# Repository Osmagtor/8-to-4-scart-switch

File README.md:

# 8-to-4 SCART Switch

<br>
<div align="center">
    <picture>
      
    </picture>
</div>
<br>

The "8-to-4 SCART Switch" is an open source PCB design for a passive SCART switch capable of (1) redirecting the signal of the selected SCART input device to the selected SCART output device and (2) selecting how the incoming signal is to be sent out (composite/RGB with composite sync or "csync"). It can accommodate for an RCA port to introduce a stereo audio signal or a lightgun signal into the selected output SCART cable.

This PCB was designed in response to the very limited number of output ports (normally 2) on the few SCART switches available for purchase that offer more than one. 

NOTE: this repository contains the KiCAD files for a PCB designed around the constraints detailed [here](#one-side-design). Thus, further adjustments may be necessary for different use-cases so feel free to modify the design so that it may better suit your needs or to expand its functionality. For this same reason, the .STL files for the case displayed in the picture above are not included.
## Table of Contents

* [PCB Breakdown](#pcb-breakdown)
	* [Multiple Inputs](#multiple-inputs)
	* [Multiple Outputs](#multiple-outputs)
	* [Multiple Inputs & Outputs](#multiple-inputs-&-outputs)
* [Known Issues & Limitations](#known-issues-&-limitations)
	* [One Side Design](#one-side-design)
	* [Single Input and Output](#single-input-and-output)
* [Links to the parts used](#links-to-the-parts-used)

## PCB Breakdown

### Multiple Inputs

The design of the board largely borrows from inexpensive dime in a dozen SCART switches that I have found in hardware stores, like the one pictured below, and whose overall quality I can vouch for after years of use.

The three spring-loaded push buttons labelled "A", "B" and "C" handle one of the SCART input ports each. These spring-loaded push buttons are made up of 18 pins grouped up in 2 columns of 3 pins each. The bottom pin in each column receives the signal from a different pin in the SCART port. Therefore, each group of 2 x 3 pins handles 2 pins, amounting to a total of 6 pins per spring-loaded push button: 

- SCART pin 2 (Right Audio In).
- SCART pin 6 (Left Audio In/ Mono Audio)
- SCART pin 7 (Blue).
- SCART pin 11 (Green).
- SCART pin 15 (Red).
- SCART pin 20 (Composite Video In).

When pushed down, the buttons connect the middle pins with the bottom pins. The incoming signal is then carried across all the other middle pins of the same type that lie between the button and the SCART output port by means of jump wires (hidden on the underside of the board behind some of the ports) and eventually makes it to the corresponding pin on the SCART output port.

It is worth noting that the "corresponding" pin is not always the same pin as in the SCART input port. The Red, Blue and Green video signals travel to the same pins. That is, they travel from pins 15, 11 and 7, respectively, to pins 15, 11 and 7. However, the Composite, Left Audio and Right Audio signals are "crosslinked". In other words, pin 20 (Composite Video In), pin 2 (Right Audio In) and pin 6 (Left Audio In/ Mono Audio) end up on pin 19 (Composite Video Out), pin 1 (Right Audio Out) and pin 3 (Left Audio Out/ Mono) at the other end of any SCART cable. This essentially means that pins 20, 2 and 6 on the SCART input ports have to be routed to pins 19, 1 and 3, respectively.

The two sets of RCA ports on the switch exploit this feature of the design of SCART cables. One of them is connected to all the output pins on the SCART output port, serving as a set of RCA input ports. This is very useful for consoles with mono audio, like the Sega MegaDrive/ Genesis, as the original mono audio signal can be replaced by the stereo audio from the console's headphone jack. Moreover, the Composite Video jack of this set can be used to introduce the signal of a lightgun in lieu of having to plug the lightgun into the TV. The other set of RCA ports is connected to all the input pins on the SCART output port, serving as a set of RCA output ports.

There is only two pins left to address: pin 8 (Status & Aspect Ratio) and pin 16 (RGB Selection). These are routed through separate common traces via 1N4148 diodes (on the underside of the board). Unlike all other pins, pins 8 and 16 carry higher voltages. Pin 8 sits between 5 and 8 V for a 16:9 aspect ratio and between 9.5 and 12 V for a 4:3 aspect ratio. Meanwhile, pin 16 sits between 0 and 0.4 V for a Composite Video Signal and between 1 and 3 V for a RGB Video signal with composite sync or "csync". 

While, the mechanism holding all spring-loaded push buttons together only allows one button to be pushed down at once, it is possible to brute force multiple switches into a pushed down state. As such, the diodes preclude any of the previous signals from feeding back into one another and causing any kind of mayhem. As to why these signals are not routed through the push buttons using sets of 24 pins instead, costs and/or availability may be to blame. When sourcing for these same type of push buttons for this project's PCB design, sets of 24 pin push buttons where much harder to come by and more expensive to boot. It could also be that the board only being printed one side, it couldn't accommodate for even more bespoke traces and all the ensuing jump wires.

Finally, the RGB push button on the switch simply allows the RGB signal through, telling the receiving device to use the signals from the RGB pins for video and the signal from the Composite Video pin as sync ("csync"). When the button is not pushed down, the RGB signal is cut off, telling the receiving device to use the signal from the Composite Video pin for the video signal. 
### Multiple Outputs

To be able to select between multiple outputs instead, it is necessary to change the directionality of the SCART switch described [above](#source-material). The necessary changes to achieve this were carried out on another identical switch by severing the necessary traces and bridging the necessary pins by means of wires. It is far from the most aesthetically-pleasing of solutions but it served as proof-of-concept.

For staters, the directionality of the crosslinked pins had to be reverted. Therefore, pin 20 (Composite Video In), pin 2 (Right Audio In) and pin 6 (Left Audio In/ Mono Audio) on the SCART input port were routed to pin 19 (Composite Video Out), pin 1 (Right Audio Out) and pin 3 (Left Audio Out/ Mono) on the SCART output ports. As the traces on the board were connected to the wrong pins, it was necessary to sever all the traces involved on either end and bypass them using spare wires. The RGB video pins, meanwhile, could be left intact since they connect to the same pins on both ends.

Pins 8 and 16 could not remain routed through their separate common traces. In their default configuration, the diodes would prevent any signal from coming through and simply changing their direction to allow for the signal to go through would defeat their purpose. After all, in doing so, all signals would go through at all times. Instead, the "RGB", "B-A" and "C-A" buttons were used to route these signals to the selected output, which involved further trace severing and wire soldering.

Therefore, to change the selected SCART output port, it was necessary to push down a button from each set. Pushing down the "C" button would send the RGB, Composite Video and Audio signals from the SCART input port to the third SCART output port, and pushing down the "C-A" button would send the Aspect Ratio and RGB-selection signal from the SCART input port to the third SCART output port too. In the photo below, you may more clearly observe how this worked. Note that the unmodified SCART switch is sitting behind and its output is daisy-chained to the SCART input port on the modified SCART switch.

The "RGB", "B-A" and "C-A" buttons were used since the "RGB" push-button was no longer needed for its intended purpose (after all, that was already handled by the same push-button on the 3-to-1 SCART switch) and the "B-A" and "C-A" push buttons were of no use to me.
### Multiple Inputs & Outputs

Designing a SCART switch with multiple input and output ports consisted of merging the design of (1) the inexpensive quality SCART switch that I had and (2) the other one whose directionality had successfully been reversed. 

The design of the area comprising the SCART input ports, the RCA ports and the RGB Selection push button was fairly straightforward. All that changed was the number of SCART ports, which was expanded from 3 to 8, and the output RCA port, which I completely removed as I had no real use for them.

As for the design of the area comprising the SCART output ports, a set of four 24 pin push buttons was used to bring into a single set of push buttons the signals that were controlled by the "RGB", "B-A" and "C-A" push buttons in the modified SCART switch.
## Known Issues & Limitations

First of all, the wiring that can be observed on the pictures [above](#merging-all-source-material) is the result of two minor design flaws that have since been corrected and a minor machining flaw:

* The traces that connect pins 8 and 16 were accidentally swapped around, requiring two traces to be severed and two wires to be soldered.
* The RCA connector was accidentally mirrored, causing a mismatch between the colours of the RCA ports and the pins they actually lead to.
* Owing to the levels of tolerance of the milling machine that made the board, two traces from the first SCART input port are permanently bridged, requiring the two traces to be severed and two wires to be soldered in their place.
### One Side Design 

Due to the sheer size of a PCB with this many ports, I only had access to machinery capable of making milled PCBs and the machinery in question could only mill on one side of the board, making it necessary to resort to jump wires like the SCART switches I used for reference.

This does not appear to affect any of the signals getting to the SCART output ports. At most, there is a nigh imperceptible loss of brightness that only my FrameMeister upscaler manages to pick up and which is only really noticeable on my Sega MegaDrive/ Genesis. Albeit it could be the result of the signal travelling over too many jump wires, this console uses a cheap RGB cable that might be to blame. The rest of my retro consoles are paired up with high quality RGB SCART cables from [Retro Gaming Cables](https://www.retrogamingcables.co.uk/).

Regardless, had it been possible to mill on the other side of the board, the pins connected by the jumper wires would have been connected to traces on the other side by means of vias. Needless to say, it would have made soldering easier and the end-result would have been nicer.

The pictures above are for you to form your own opinion. They are screenshots taken using a FrameMeister upscaler. The only difference between each screenshot lies on how far the SCART signal has had to travel: 

* "Frameister" means that the console's SCART cable has been directly plugged into the FrameMeister.
* "Switch v1" refers to the proof-of-concept switch that was modified to have its directionality reversed. In this case, the console's SCART cable was plugged into the unmodified switch, which, in turn, was daisy-chained into the modified switch whose output was then plugged into the FrameMeister.
* "Switch v2" refers to this project's switch.

In both cases, for "longest distance" screenshots the console's SCART cable and the SCART output cable have been set as far apart as possible, forcing the signal to travel the greatest length of jump wires possible. For "shortest distance" screenshots both cables have been set as close as possible to one another so that the signal has to travel the least. 

To my untrained eye, this does not appear to make much of a difference, not even in "Switch v1" screenshots, where the signal had to travel through an extra SCART cable connecting two switches.
### Single Input and Output

As a passive SCART switch by design, it is not possible to redirect the selected SCART input device to more than one SCART  output device. While more than one push button can be brute forced into a pushed down state, it would be necessary to boost the incoming image somehow for it to show correctly or even show at all in all devices. This would require a source of external power.

Lastly, due to the simplicity of the design of the board, it is not possible to mix and match inputs and outputs. A single selected input can only be routed to a single selected output.
## Links to the parts used

* [1x RCA port](https://es.aliexpress.com/item/1005006295411086.html?algo_exp_id=1704070b-437d-4806-bd52-9b4e4fd31481-30&pdp_npi=4%40dis%21EUR%215.68%211.82%21%21%2143.37%2113.88%21%40211b612517121802582044392eeff7%2112000036647428960%21sea%21ES%214782931422%21&curPageLogUid=3xNMGX6dJbsL&utparam-url=scene%3Asearch%7Cquery_from%3A)
* [12x female SCART ports](https://es.aliexpress.com/item/1005006636475708.html?algo_exp_id=9e1a5876-f124-43f7-b40c-11d20e1f46cf-22&pdp_npi=4%40dis%21EUR%211.55%211.45%21%21%211.63%211.52%21%40211b617a17121800592552603eb1fc%2112000037887909284%21sea%21ES%214782931422%21&curPageLogUid=zIvDoxFjqDd9&utparam-url=scene%3Asearch%7Cquery_from%3A)
* [1x 8 pin spring-loaded push button](https://es.aliexpress.com/item/1005006186944454.html?pvid=55b27e62-d06f-4987-be3b-784640dc741e&_t=gps-id%3ApcDetailTopMoreOtherSeller%2Cscm-url%3A1007.40000.327270.0%2Cpvid%3A55b27e62-d06f-4987-be3b-784640dc741e%2Ctpp_buckets%3A668%232846%238111%231996&pdp_npi=4%40dis%21EUR%213.44%211.03%21%21%2126.29%217.89%21%402103871e17121795811912119eab58%2112000036185800227%21rec%21ES%214782931422%21&utparam-url=scene%3ApcDetailTopMoreOtherSeller%7Cquery_from%3A)
* [1 set of 8 18 pin spring-loaded push buttons](https://es.aliexpress.com/item/32977337144.html?pvid=ed7a91a2-8967-4df6-9983-d61c363a6160&_t=gps-id%3ApcDetailTopMoreOtherSeller%2Cscm-url%3A1007.40000.327270.0%2Cpvid%3Aed7a91a2-8967-4df6-9983-d61c363a6160%2Ctpp_buckets%3A668%232846%238110%231995&pdp_npi=4%40dis%21EUR%212.83%212.83%21%21%212.98%212.98%21%402103871e17121797616365716eab58%2112000030624642228%21rec%21ES%214782931422%21&utparam-url=scene%3ApcDetailTopMoreOtherSeller%7Cquery_from%3A)
* [1 set of 4 24 pin spring-loaded push buttons](https://es.aliexpress.com/item/1005005575498175.html?gatewayAdapt=glo2esp)

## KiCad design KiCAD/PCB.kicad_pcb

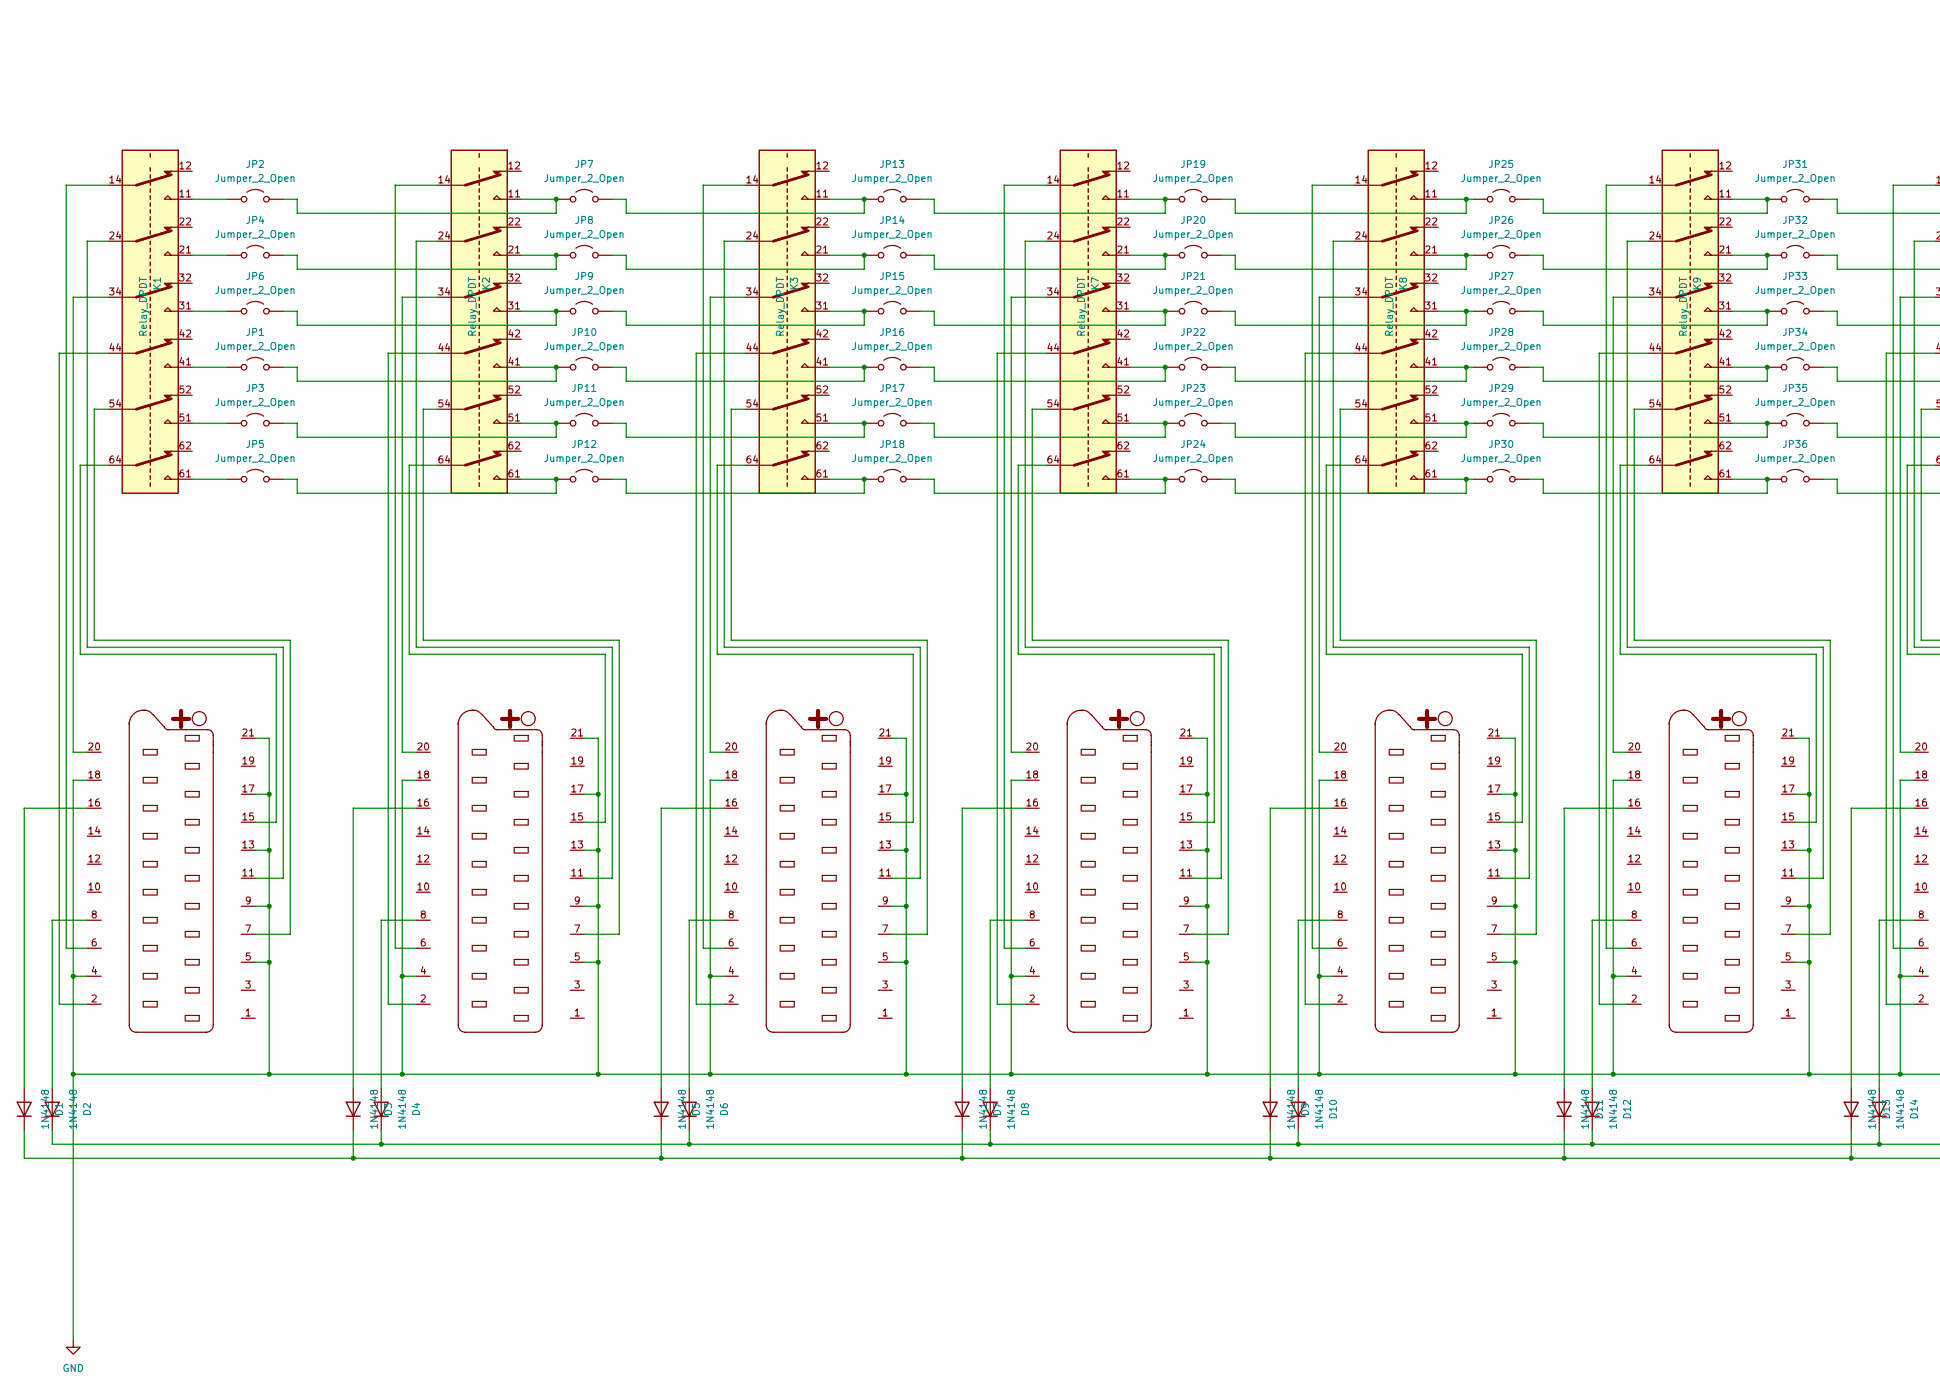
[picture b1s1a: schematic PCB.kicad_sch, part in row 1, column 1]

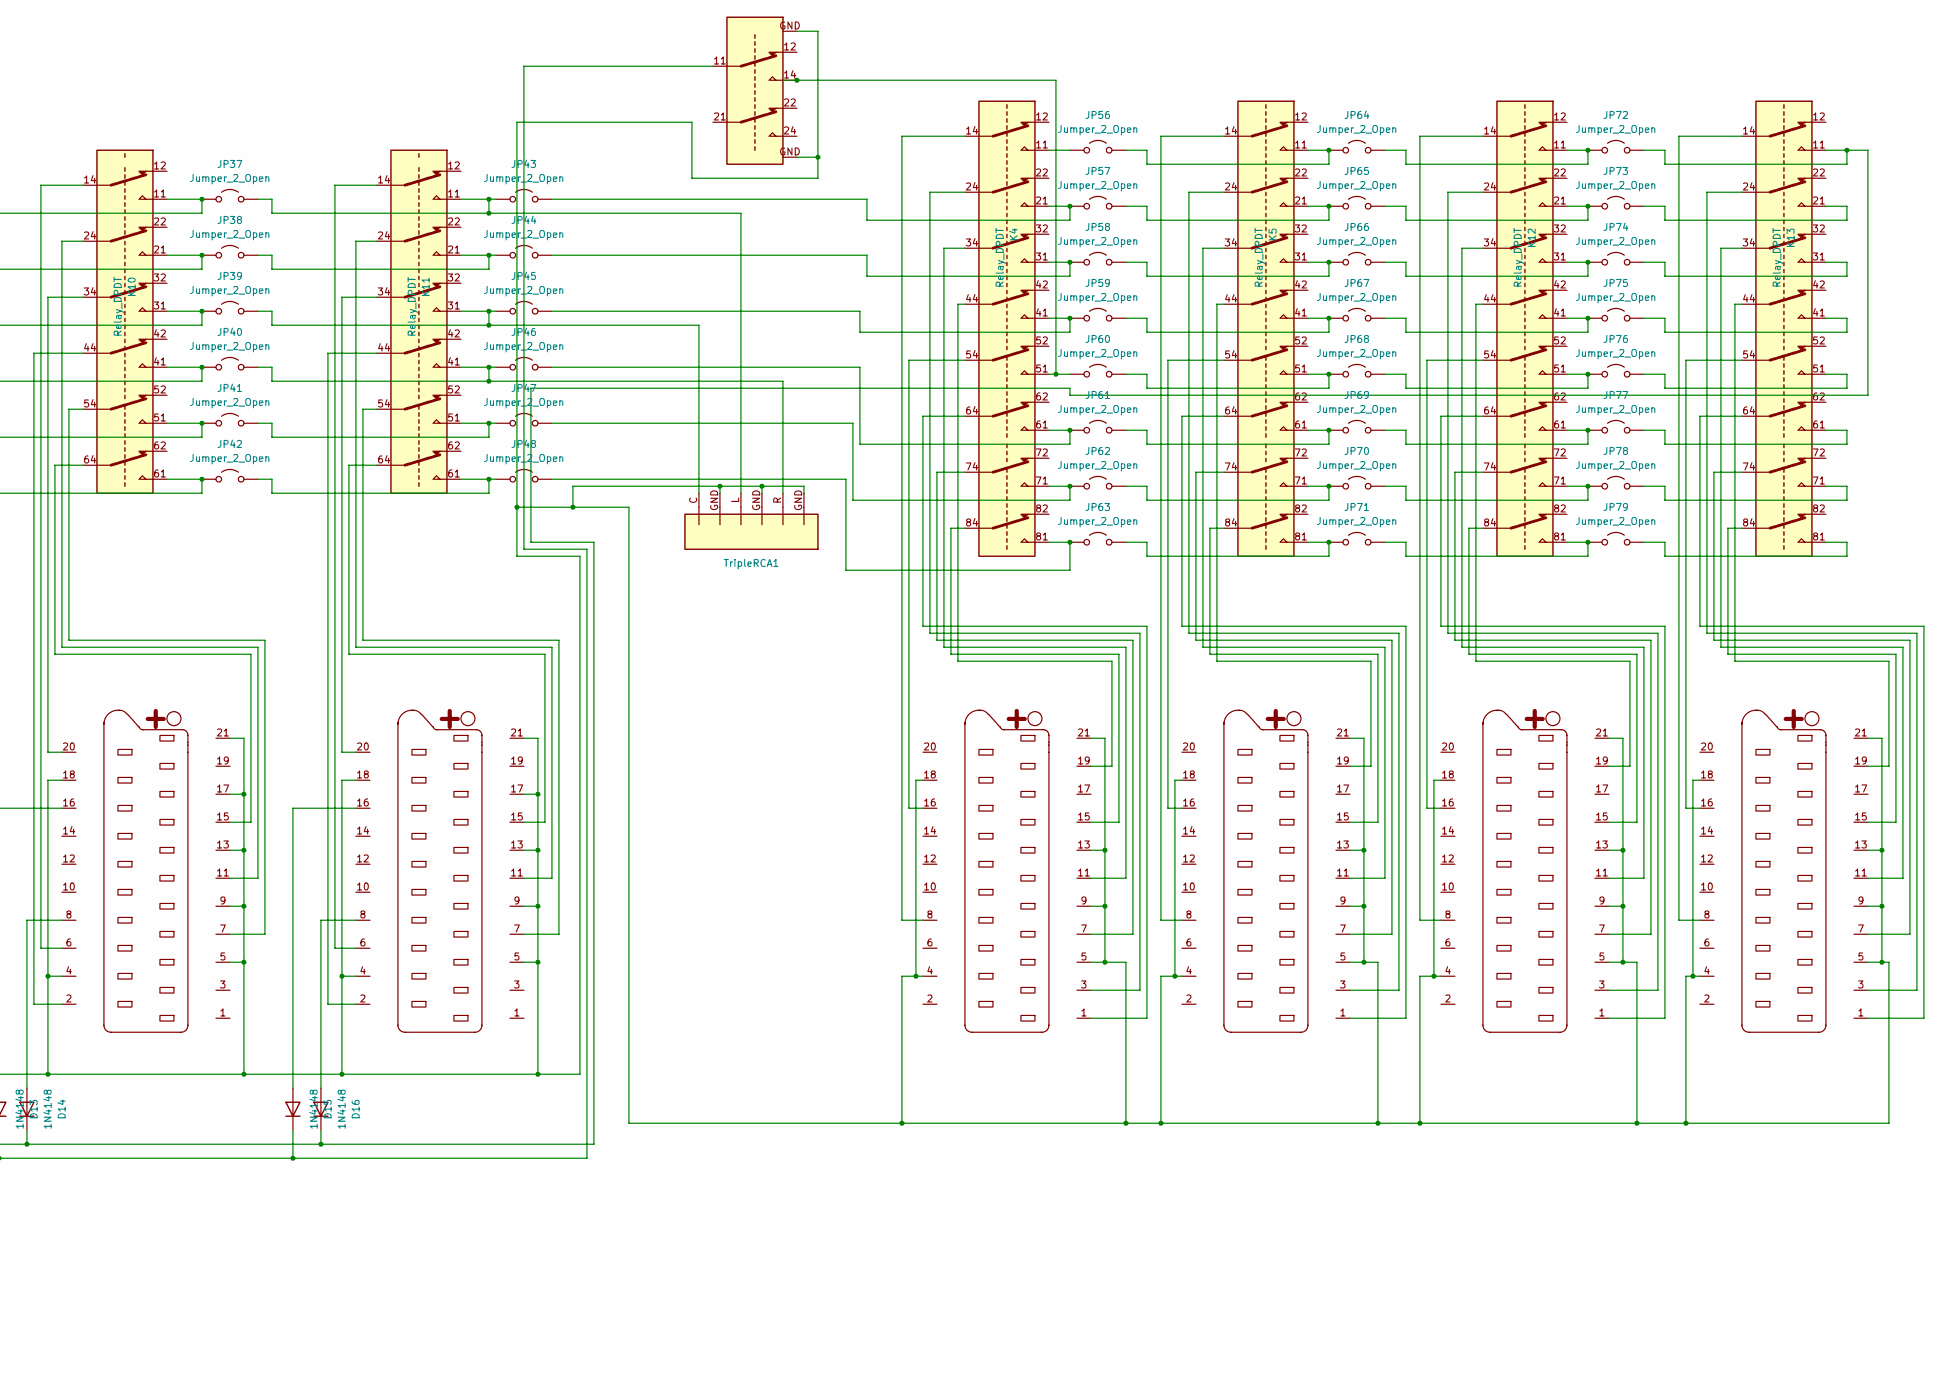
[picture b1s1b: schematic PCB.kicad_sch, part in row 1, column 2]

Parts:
D1, D2, D3, D4, D5, D6, D7, D8, D9, D10, D11, D12, D13, D14, D15, D16: 1N4148; D_DO-35_SOD27_P7.62mm_Horizontal
J1, J2, J3, J4, J5, J6, J7, J8, J9, J10, J11, J12: SCART-F; SCART
JP1, JP2, JP3, JP4, JP5, JP6, JP7, JP8, JP9, JP10, JP11, JP12, JP13, JP14, JP15, JP16, JP17, JP18, JP19, JP20, JP21, JP22, JP23, JP24, JP25, JP26, JP27, JP28, JP29, JP30, JP31, JP32, JP33, JP34, JP35, JP36, JP37, JP38, JP39, JP40, JP41, JP42, JP56, JP57, JP58, JP59, JP60, JP61, JP62, JP63, JP64, JP65, JP66, JP67, JP68, JP69, JP70, JP71, JP72, JP73, JP74, JP75, JP76, JP77, JP78, JP79: Jumper_2_Open; Jumper-Wire_12mm_Red
JP43, JP44, JP45, JP46, JP47, JP48: Jumper_2_Open; Jumper-Wire_20mm_Blue
K1, K2, K3, K7, K8, K9, K10, K11: Relay_DPDT; 18-PIN RELAY
K4, K5, K12, K13: Relay_DPDT; 24-PIN RELAY
K6: Relay_DPDT; Relay_DPDT_RGB_ONOFF
TripleRCA1: Triple_RCA

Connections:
GND: J1.4, J1.5, J1.9, J1.13, J1.17, J1.18, J1.21, J2.4, J2.5, J2.9, J2.13, J2.17, J2.18, J2.21, J3.4, J3.5, J3.9, J3.13, J3.17, J3.18, J3.21, J4.4, J4.5, J4.9, J4.13, J4.18, J4.21, J5.4, J5.5, J5.9, J5.13, J5.18, J5.21, J6.4, J6.5, J6.9, J6.13, J6.17, J6.18, J6.21, J7.4, J7.5, J7.9, J7.13, J7.17, J7.18, J7.21, J8.4, J8.5, J8.9, J8.13, J8.17, J8.18, J8.21, J9.4, J9.5, J9.9, J9.13, J9.17, J9.18, J9.21, J10.4, J10.5, J10.9, J10.13, J10.17, J10.18, J10.21, J11.4, J11.5, J11.9, J11.13, J11.18, J11.21, J12.4, J12.5, J12.9, J12.13, J12.18, J12.21, K6.GND, TripleRCA1.GND
unnamed: D1.2 (A), J1.16
unnamed: D1.1 (K), D3.1 (K), D5.1 (K), D7.1 (K), D9.1 (K), D11.1 (K), D13.1 (K), D15.1 (K), K6.11
unnamed: D2.2 (A), J1.8
unnamed: D3.2 (A), J2.16
unnamed: D4.2 (A), J2.8
unnamed: D5.2 (A), J3.16
unnamed: D6.2 (A), J3.8
unnamed: D7.2 (A), J6.16
unnamed: D8.2 (A), J6.8
unnamed: D9.2 (A), J7.16
unnamed: D10.2 (A), J7.8
unnamed: D2.1 (K), D4.1 (K), D6.1 (K), D8.1 (K), D10.1 (K), D12.1 (K), D14.1 (K), D16.1 (K), JP72.2 (B), K13.11
unnamed: D11.2 (A), J8.16
unnamed: D12.2 (A), J8.8
unnamed: D13.2 (A), J9.16
unnamed: D14.2 (A), J9.8
unnamed: D15.2 (A), J10.16
unnamed: D16.2 (A), J10.8
unnamed: J1.2, K1.44
unnamed: J1.6, K1.14
unnamed: J1.7, K1.54
unnamed: J1.11, K1.24
unnamed: J1.15, K1.64
unnamed: J1.20, K1.34
unnamed: J2.2, K2.44
unnamed: J2.6, K2.14
unnamed: J2.7, K2.54
unnamed: J2.11, K2.24
unnamed: J2.15, K2.64
unnamed: J2.20, K2.34
unnamed: J3.2, K3.44
unnamed: J3.6, K3.14
unnamed: J3.7, K3.54
unnamed: J3.11, K3.24
unnamed: J3.15, K3.64
unnamed: J3.20, K3.34
unnamed: J4.1, K4.64
unnamed: J4.3, K4.24
unnamed: J4.7, K4.74
unnamed: J4.8, K4.14
unnamed: J4.11, K4.34
unnamed: J4.15, K4.84
unnamed: J4.16, K4.54
unnamed: J4.19, K4.44
unnamed: J5.1, K5.64
unnamed: J5.3, K5.24
unnamed: J5.7, K5.74
unnamed: J5.8, K5.14
unnamed: J5.11, K5.34
unnamed: J5.15, K5.84
unnamed: J5.16, K5.54
unnamed: J5.19, K5.44
unnamed: J6.2, K7.44
unnamed: J6.6, K7.14
unnamed: J6.7, K7.54
unnamed: J6.11, K7.24
unnamed: J6.15, K7.64
unnamed: J6.20, K7.34
unnamed: J7.2, K8.44
unnamed: J7.6, K8.14
unnamed: J7.7, K8.54
unnamed: J7.11, K8.24
unnamed: J7.15, K8.64
unnamed: J7.20, K8.34
unnamed: J8.2, K9.44
unnamed: J8.6, K9.14
unnamed: J8.7, K9.54
unnamed: J8.11, K9.24
unnamed: J8.15, K9.64
unnamed: J8.20, K9.34
unnamed: J9.2, K10.44
unnamed: J9.6, K10.14
unnamed: J9.7, K10.54
unnamed: J9.11, K10.24
unnamed: J9.15, K10.64
unnamed: J9.20, K10.34
unnamed: J10.2, K11.44
unnamed: J10.6, K11.14
unnamed: J10.7, K11.54
unnamed: J10.11, K11.24
unnamed: J10.15, K11.64
unnamed: J10.20, K11.34
unnamed: J11.1, K12.64
unnamed: J11.3, K12.24
unnamed: J11.7, K12.74
unnamed: J11.8, K12.14
unnamed: J11.11, K12.34
unnamed: J11.15, K12.84
unnamed: J11.16, K12.54
unnamed: J11.19, K12.44
unnamed: J12.1, K13.64
unnamed: J12.3, K13.24
unnamed: J12.7, K13.74
unnamed: J12.8, K13.14
unnamed: J12.11, K13.34
unnamed: J12.15, K13.84
unnamed: J12.16, K13.54
unnamed: J12.19, K13.44
unnamed: JP1.1 (A), K1.41
unnamed: JP1.2 (B), JP10.1 (A), K2.41
unnamed: JP2.1 (A), K1.11
unnamed: JP2.2 (B), JP7.1 (A), K2.11
unnamed: JP3.1 (A), K1.51
unnamed: JP4.1 (A), K1.21
unnamed: JP4.2 (B), JP8.1 (A), K2.21
unnamed: JP5.1 (A), K1.61
unnamed: JP6.1 (A), K1.31
unnamed: JP6.2 (B), JP9.1 (A), K2.31
unnamed: JP10.2 (B), JP16.1 (A), K3.41
unnamed: JP3.2 (B), JP11.1 (A), K2.51
unnamed: JP11.2 (B), JP17.1 (A), K3.51
unnamed: JP5.2 (B), JP12.1 (A), K2.61
unnamed: JP12.2 (B), JP18.1 (A), K3.61
unnamed: JP7.2 (B), JP13.1 (A), K3.11
unnamed: JP13.2 (B), JP19.1 (A), K7.11
unnamed: JP8.2 (B), JP14.1 (A), K3.21
unnamed: JP14.2 (B), JP20.1 (A), K7.21
unnamed: JP9.2 (B), JP15.1 (A), K3.31
unnamed: JP15.2 (B), JP21.1 (A), K7.31
unnamed: JP16.2 (B), JP22.1 (A), K7.41
unnamed: JP17.2 (B), JP23.1 (A), K7.51
unnamed: JP18.2 (B), JP24.1 (A), K7.61
unnamed: JP19.2 (B), JP25.1 (A), K8.11
unnamed: JP20.2 (B), JP26.1 (A), K8.21
unnamed: JP21.2 (B), JP27.1 (A), K8.31
unnamed: JP22.2 (B), JP28.1 (A), K8.41
unnamed: JP23.2 (B), JP29.1 (A), K8.51
unnamed: JP24.2 (B), JP30.1 (A), K8.61
unnamed: JP25.2 (B), JP31.1 (A), K9.11
unnamed: JP26.2 (B), JP32.1 (A), K9.21
unnamed: JP27.2 (B), JP33.1 (A), K9.31
unnamed: JP28.2 (B), JP34.1 (A), K9.41
unnamed: JP29.2 (B), JP35.1 (A), K9.51
unnamed: JP30.2 (B), JP36.1 (A), K9.61
unnamed: JP31.2 (B), JP37.1 (A), K10.11
unnamed: JP32.2 (B), JP38.1 (A), K10.21
unnamed: JP33.2 (B), JP39.1 (A), K10.31
unnamed: JP34.2 (B), JP40.1 (A), K10.41
unnamed: JP35.2 (B), JP41.1 (A), K10.51
unnamed: JP36.2 (B), JP42.1 (A), K10.61
unnamed: JP37.2 (B), JP43.1 (A), K11.11, TripleRCA1.L
unnamed: JP38.2 (B), JP44.1 (A), K11.21
unnamed: JP39.2 (B), JP45.1 (A), K11.31, TripleRCA1.C
unnamed: JP40.2 (B), JP46.1 (A), K11.41, TripleRCA1.R
unnamed: JP41.2 (B), JP47.1 (A), K11.51
unnamed: JP42.2 (B), JP48.1 (A), K11.61
unnamed: JP43.2 (B), JP57.1 (A), K4.21
unnamed: JP44.2 (B), JP58.1 (A), K4.31
unnamed: JP45.2 (B), JP59.1 (A), K4.41
unnamed: JP46.2 (B), JP61.1 (A), K4.61
unnamed: JP47.2 (B), JP62.1 (A), K4.71
unnamed: JP48.2 (B), JP63.1 (A), K4.81
unnamed: JP56.1 (A), K4.11
unnamed: JP56.2 (B), JP64.1 (A), K5.11
unnamed: JP57.2 (B), JP65.1 (A), K5.21
unnamed: JP58.2 (B), JP66.1 (A), K5.31
unnamed: JP59.2 (B), JP67.1 (A), K5.41
unnamed: JP60.1 (A), K4.51, K6.14
unnamed: JP60.2 (B), JP68.1 (A), K5.51
unnamed: JP61.2 (B), JP69.1 (A), K5.61
unnamed: JP62.2 (B), JP70.1 (A), K5.71
unnamed: JP63.2 (B), JP71.1 (A), K5.81
unnamed: JP64.2 (B), JP72.1 (A), K12.11
unnamed: JP65.2 (B), JP73.1 (A), K12.21
unnamed: JP66.2 (B), JP74.1 (A), K12.31
unnamed: JP67.2 (B), JP75.1 (A), K12.41
unnamed: JP68.2 (B), JP76.1 (A), K12.51
unnamed: JP69.2 (B), JP77.1 (A), K12.61
unnamed: JP70.2 (B), JP78.1 (A), K12.71
unnamed: JP71.2 (B), JP79.1 (A), K12.81
unnamed: JP73.2 (B), K13.21
unnamed: JP74.2 (B), K13.31
unnamed: JP75.2 (B), K13.41
unnamed: JP76.2 (B), K13.51
unnamed: JP77.2 (B), K13.61
unnamed: JP78.2 (B), K13.71
unnamed: JP79.2 (B), K13.81

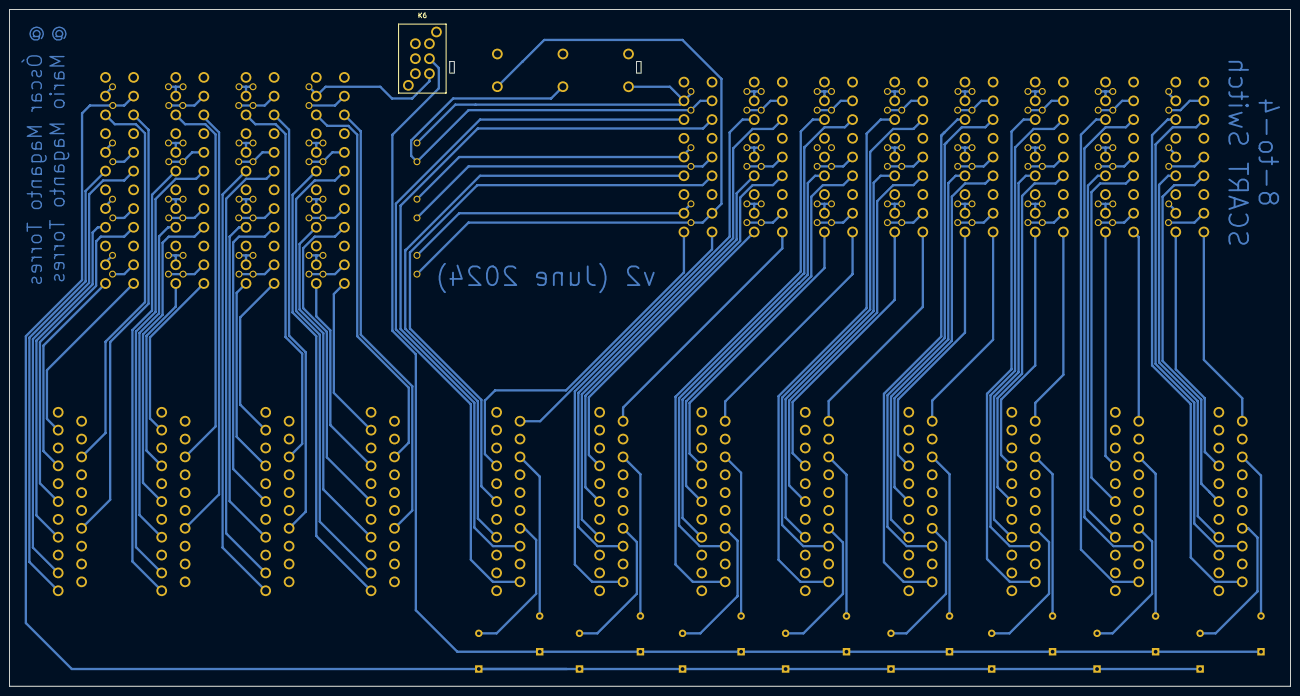
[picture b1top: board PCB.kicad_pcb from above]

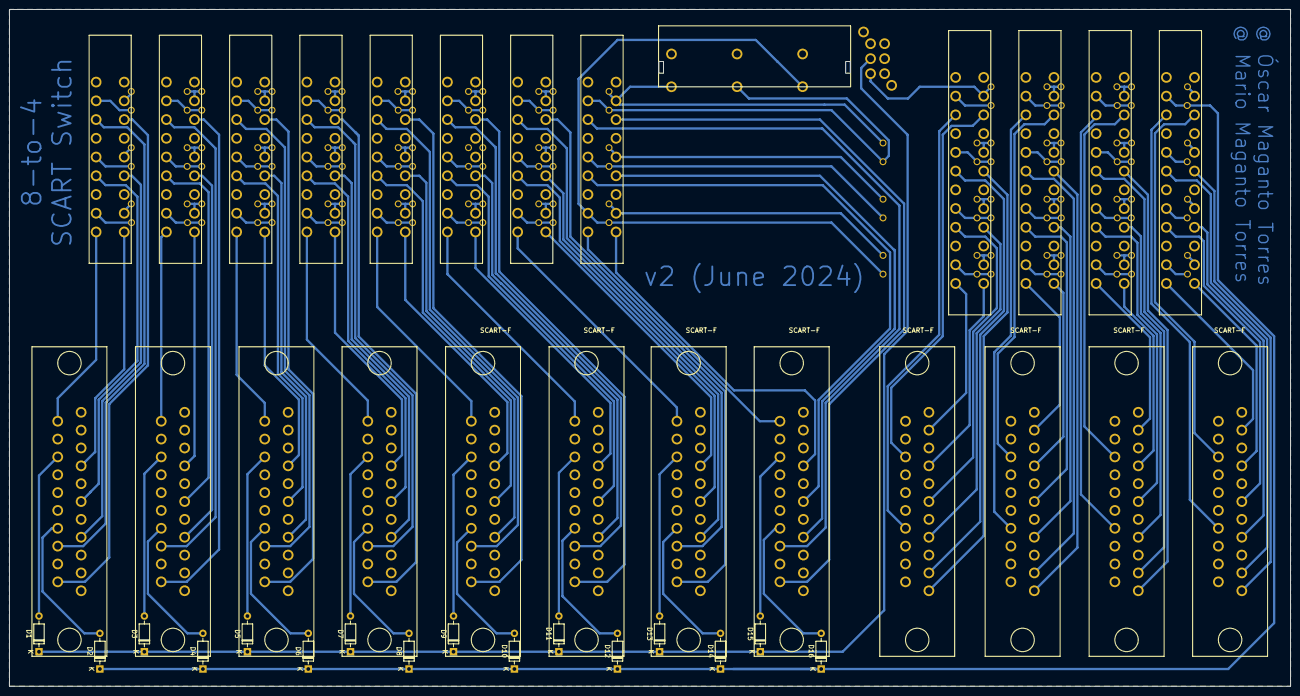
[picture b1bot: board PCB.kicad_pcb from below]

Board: 2 copper layers, 273.5 x 144.5 mm, 114 parts (112 on the bottom side), 178 nets.

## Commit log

2024-07-24 Add files via upload
    Game console screenshots
2024-07-24 KiCAD files
    KiCAD files
2024-07-24 KiCAD files, PCB photos and game console screenshots
2024-09-15 Update LICENSE
2026-04-19 Add Ko-fi button to README
    Added a Ko-fi button for support and updated the README.
2026-04-19 Enhance README with donation button and formatting
    Added a centered Ko-fi button for donations and improved formatting.
